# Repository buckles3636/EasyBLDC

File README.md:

# Easy BLDC

## Overview
Easy BLDC is an open source sensorless FOC brushless dc motor driver designed for propeller thrust applications such as drones or underwater AUVS.

## Features
* 30V Maximum Input Voltage
* 20A Maximum Continues Current (Untested)
* High current Amphenol power blade connector for board-board mounting
* High efficency FOC algorithm
* Modifiable parameters via Ti MotorWare® GUI

## Why FOC?
FOC is the most advanced of the three common algorithms. Unlike trapezoidal or sinusoidal control, which energize the motor’s phases based on predefined waveforms, FOC actively keeps tracks the stator position. This allows for precise control of both torque and speed by decoupling the motor’s magnetic field into two components: one that controls the motor's flux and the other that controls the torque. FOC is extremely efficient, especially at higher speeds, and results in smooth operation at lower speeds. 

## Key Components
* Texas Instruments DRV8305 gate driver
* Texas Instruments InstaSpin® TMS320F28027F MCU

## Ordering Guide
TODO:

## Getting Started Guide
TODO:

## Motor Tuning Guide
TODO:

## Contribution Guidelines
We welcome contributions from the broader community. To contribute:

1. **Fork the Repository**: Create your own fork of the project.
2. **Create a Feature Branch**: Make your changes in a new branch.
3. **Commit Your Changes**: Commit your changes with clear and detailed commit messages.
4. **Submit a Pull Request**: Create a pull request for your changes to be reviewed.

Please ensure your designs meet common standards and include necessary documentation and comments.

## Project Status
- Version 1: Released
- Version 2: In  Progress

## License
This project is licensed under the [MIT License](LICENSE) - see the LICENSE file for details.

## Contact
- Designer: Peter Buckley
- Email: peterbuckley3636@gmail.com

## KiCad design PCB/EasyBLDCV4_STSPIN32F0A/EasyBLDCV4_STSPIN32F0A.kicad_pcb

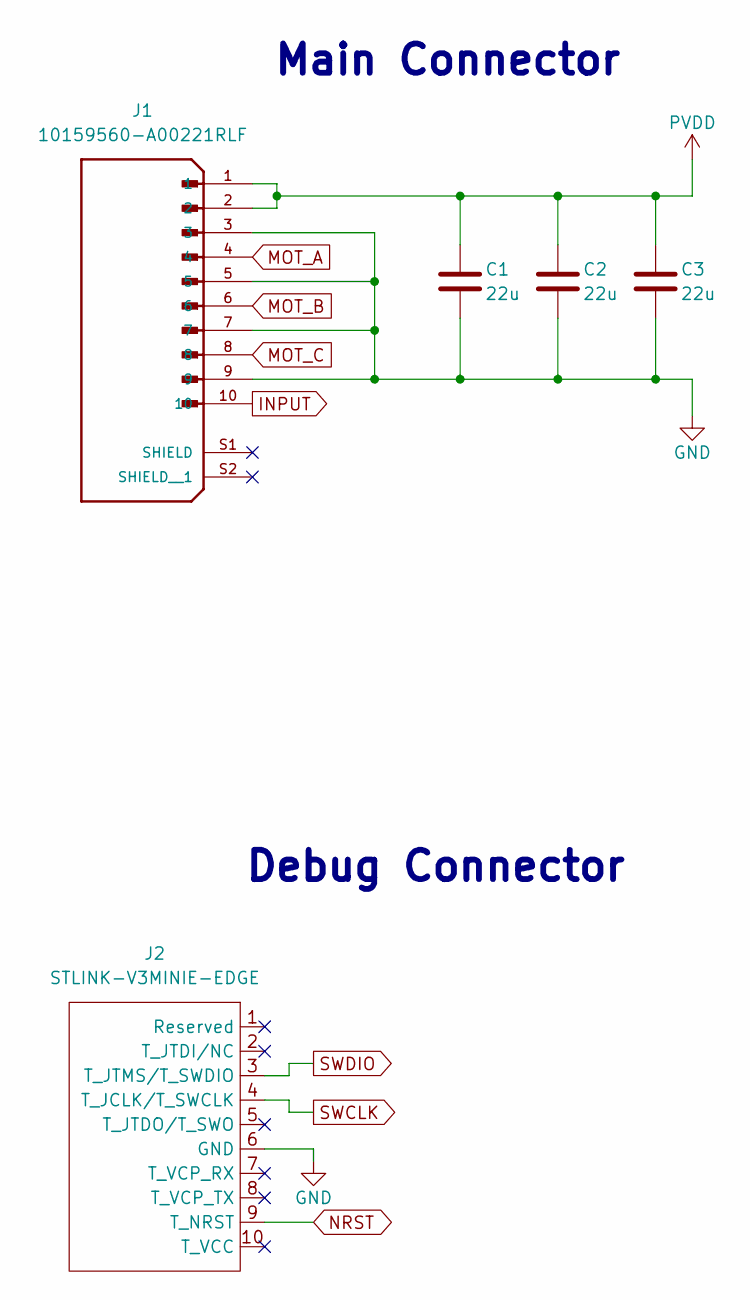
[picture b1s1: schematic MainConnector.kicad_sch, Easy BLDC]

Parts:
C1, C2, C3: 22u; C_1206_3216Metric
J1: 10159560-A00221RLF; AMPHENOL_10159560-A00221RLF; PARTREV C
J2: STLINK-V3MINIE-EDGE

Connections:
GND: C1.2, C2.2, C3.2, J1.3, J1.5, J1.7, J1.9, J2.6 (GND); also elsewhere on the board
INPUT: J1.10
MOT_A: J1.4; also elsewhere on the board
MOT_B: J1.6; also elsewhere on the board
MOT_C: J1.8; also elsewhere on the board
NRST: J2.9 (T_NRST); also elsewhere on the board
PVDD: C1.1, C2.1, C3.1, J1.1, J1.2; also elsewhere on the board
SWCLK: J2.4 (T_JCLK/T_SWCLK); also elsewhere on the board
SWDIO: J2.3 (T_JTMS/T_SWDIO); also elsewhere on the board

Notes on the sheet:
Main Connector
Debug Connector

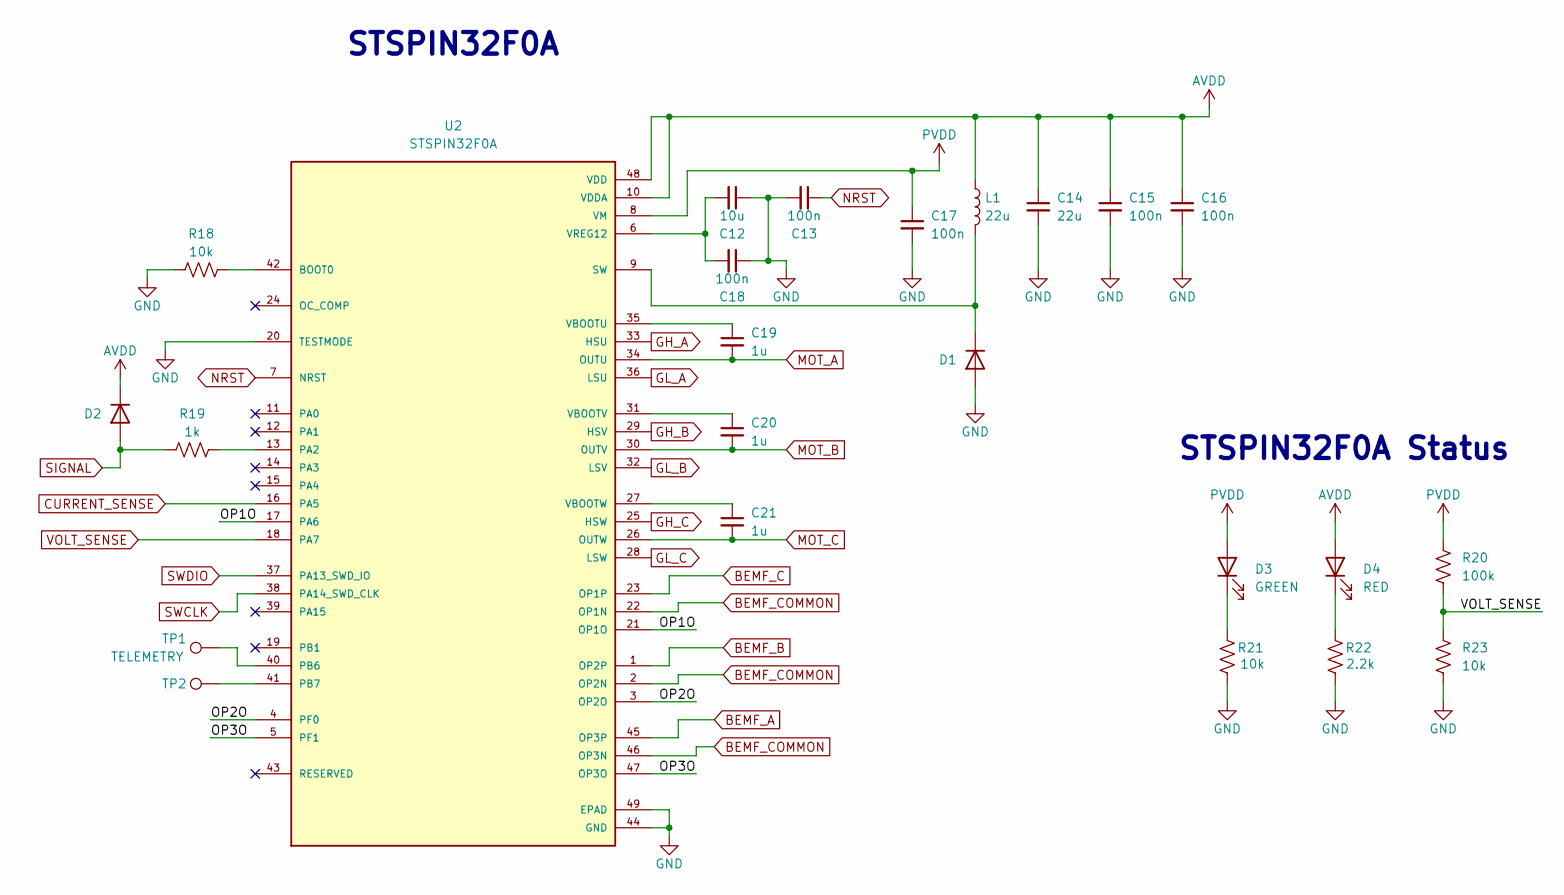
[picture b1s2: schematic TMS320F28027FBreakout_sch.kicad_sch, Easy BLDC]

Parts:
C12: 10u; C_0805_2012Metric
C13, C15, C16, C17, C18: 100n; C_0402_1005Metric
C14: 22u; C_0805_2012Metric
C19, C20, C21: 1u; C_0402_1005Metric
D1, D2: D; D_0402_1005Metric
D3: GREEN; LED_0603_1608Metric
D4: RED; LED_0603_1608Metric
L1: 22u; L_0805_2012Metric
R18, R21, R23: 10k; R_0402_1005Metric
R19: 1k; R_0402_1005Metric
R20: 100k; R_0402_1005Metric
R22: 2.2k; R_0402_1005Metric
TP1: TELEMETRY; TestPoint_Pad_D1.5mm
TP2: TestPoint; TestPoint_Pad_D1.5mm
U2: STSPIN32F0A; IC_STSPIN32F0A; PARTREV 2

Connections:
/MCU/OP1O: U2.17 (PA6), U2.21 (OP1O)
/MCU/OP2O: U2.3 (OP2O), U2.4 (PF0)
/MCU/OP3O: U2.5 (PF1), U2.47 (OP3O)
AVDD: C14.1, C15.1, C16.1, D2.1 (K), D4.2 (A), L1.1, U2.10 (VDDA), U2.48 (VDD); also elsewhere on the board
BEMF_A: U2.45 (OP3P); also elsewhere on the board
BEMF_B: U2.1 (OP2P); also elsewhere on the board
BEMF_C: U2.23 (OP1P); also elsewhere on the board
BEMF_COMMON: U2.2 (OP2N), U2.22 (OP1N), U2.46 (OP3N); also elsewhere on the board
CURRENT_SENSE: U2.16 (PA5); also elsewhere on the board
GH_A: U2.33 (HSU); also elsewhere on the board
GH_B: U2.29 (HSV); also elsewhere on the board
GH_C: U2.25 (HSW); also elsewhere on the board
GL_A: U2.36 (LSU); also elsewhere on the board
GL_B: U2.32 (LSV); also elsewhere on the board
GL_C: U2.28 (LSW); also elsewhere on the board
GND: C12.1, C13.2, C14.2, C15.2, C16.2, C17.2, C18.1, D1.2 (A), R18.1, R21.1, R22.1, R23.2, U2.20 (TESTMODE), U2.44 (GND), U2.49 (EPAD); also elsewhere on the board
MOT_A: C19.2, U2.34 (OUTU); also elsewhere on the board
MOT_B: C20.2, U2.30 (OUTV); also elsewhere on the board
MOT_C: C21.2, U2.26 (OUTW); also elsewhere on the board
NRST: C13.1, U2.7 (NRST); also elsewhere on the board
unnamed: D1.1 (K), L1.2, U2.9 (SW)
unnamed: D3.1 (K), R21.2
unnamed: D4.1 (K), R22.2
unnamed: R18.2, U2.42 (BOOT0)
unnamed: R19.2, U2.13 (PA2)
unnamed: TP1.1, U2.40 (PB6)
unnamed: TP2.1, U2.41 (PB7)
unnamed: C19.1, U2.35 (VBOOTU)
unnamed: C20.1, U2.31 (VBOOTV)
unnamed: C21.1, U2.27 (VBOOTW)
unnamed: C12.2, C18.2, U2.6 (VREG12)
PVDD: C17.1, D3.2 (A), R20.1, U2.8 (VM); also elsewhere on the board
SIGNAL: D2.2 (A), R19.1
SWCLK: U2.38 (PA14_SWD_CLK); also elsewhere on the board
SWDIO: U2.37 (PA13_SWD_IO); also elsewhere on the board
VOLT_SENSE: R20.2, R23.1, U2.18 (PA7)

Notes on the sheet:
STSPIN32F0A Status
STSPIN32F0A

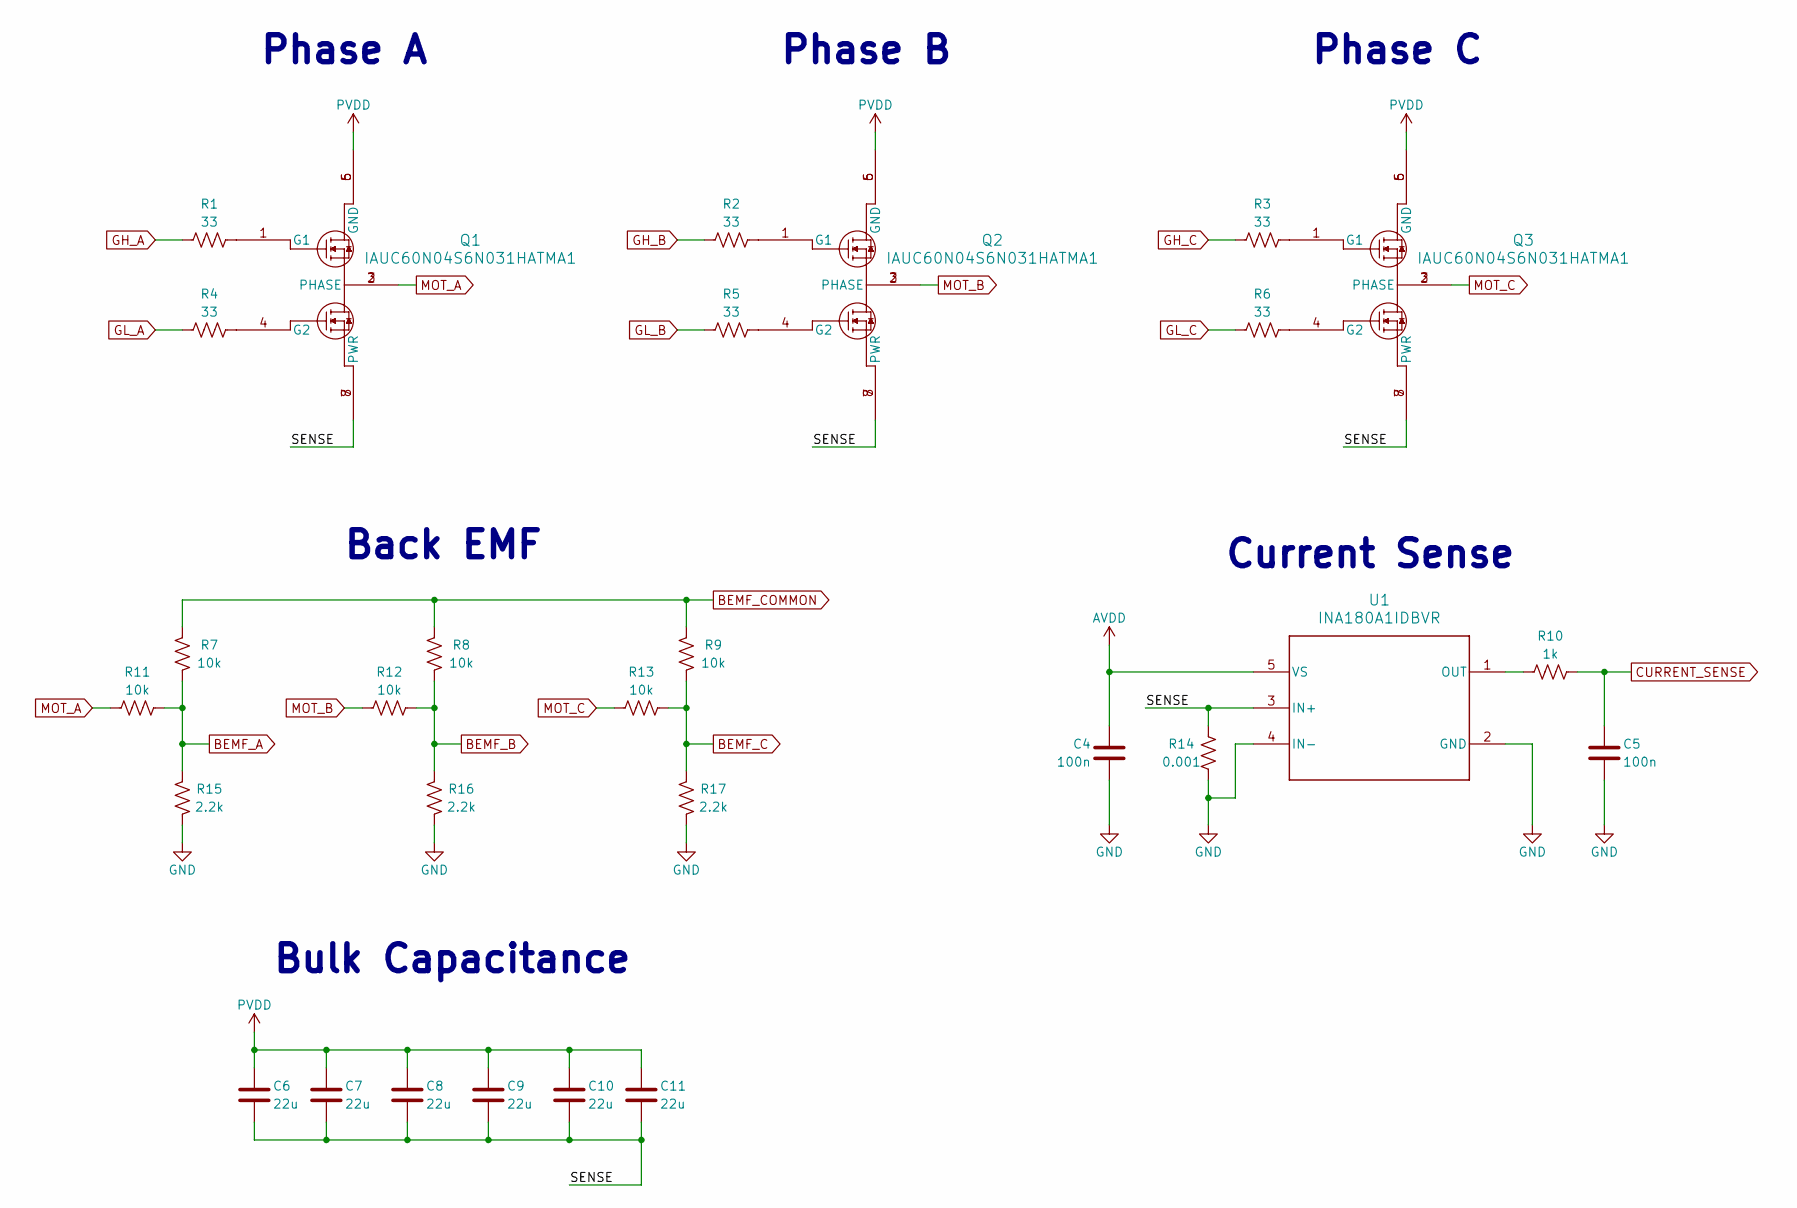
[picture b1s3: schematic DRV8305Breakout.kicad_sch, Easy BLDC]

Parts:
C4, C5: 100n; C_0402_1005Metric
C6, C7, C8, C9, C10, C11: 22u; C_1206_3216Metric
Q1, Q2, Q3: IAUC60N04S6N031HATMA1; PG-TDSON-8-56-2
R1, R2, R3, R4, R5, R6: 33; R_0402_1005Metric
R7, R8, R9, R11, R12, R13: 10k; R_0402_1005Metric
R10: 1k; R_0402_1005Metric
R14: 0.001; R_2512_6332Metric
R15, R16, R17: 2.2k; R_0402_1005Metric
U1: INA180A1IDBVR; DBV0005A_N

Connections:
/Power Stage/SENSE: C6.2, C7.2, C8.2, C9.2, C10.2, C11.2, Q1.7 (PWR), Q1.8 (PWR), Q2.7 (PWR), Q2.8 (PWR), Q3.7 (PWR), Q3.8 (PWR), R14.2, U1.3 (IN+)
AVDD: C4.1, U1.5 (VS); also elsewhere on the board
BEMF_A: R7.1, R11.2, R15.2; also elsewhere on the board
BEMF_B: R8.1, R12.2, R16.2; also elsewhere on the board
BEMF_C: R9.1, R13.2, R17.2; also elsewhere on the board
BEMF_COMMON: R7.2, R8.2, R9.2; also elsewhere on the board
CURRENT_SENSE: C5.1, R10.2; also elsewhere on the board
GH_A: R1.1; also elsewhere on the board
GH_B: R2.1; also elsewhere on the board
GH_C: R3.1; also elsewhere on the board
GL_A: R4.1; also elsewhere on the board
GL_B: R5.1; also elsewhere on the board
GL_C: R6.1; also elsewhere on the board
GND: C4.2, C5.2, R14.1, R15.1, R16.1, R17.1, U1.2 (GND), U1.4 (IN-); also elsewhere on the board
MOT_A: Q1.2 (PHASE), Q1.3 (PHASE), R11.1; also elsewhere on the board
MOT_B: Q2.2 (PHASE), Q2.3 (PHASE), R12.1; also elsewhere on the board
MOT_C: Q3.2 (PHASE), Q3.3 (PHASE), R13.1; also elsewhere on the board
unnamed: Q1.1 (G1), R1.2
unnamed: Q1.4 (G2), R4.2
unnamed: Q2.1 (G1), R2.2
unnamed: Q2.4 (G2), R5.2
unnamed: Q3.1 (G1), R3.2
unnamed: Q3.4 (G2), R6.2
unnamed: R10.1, U1.1 (OUT)
PVDD: C6.1, C7.1, C8.1, C9.1, C10.1, C11.1, Q1.5 (GND), Q1.6 (GND), Q2.5 (GND), Q2.6 (GND), Q3.5 (GND), Q3.6 (GND); also elsewhere on the board

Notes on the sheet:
Current Sense
Phase C
Bulk Capacitance
Phase B
Back EMF
Phase A

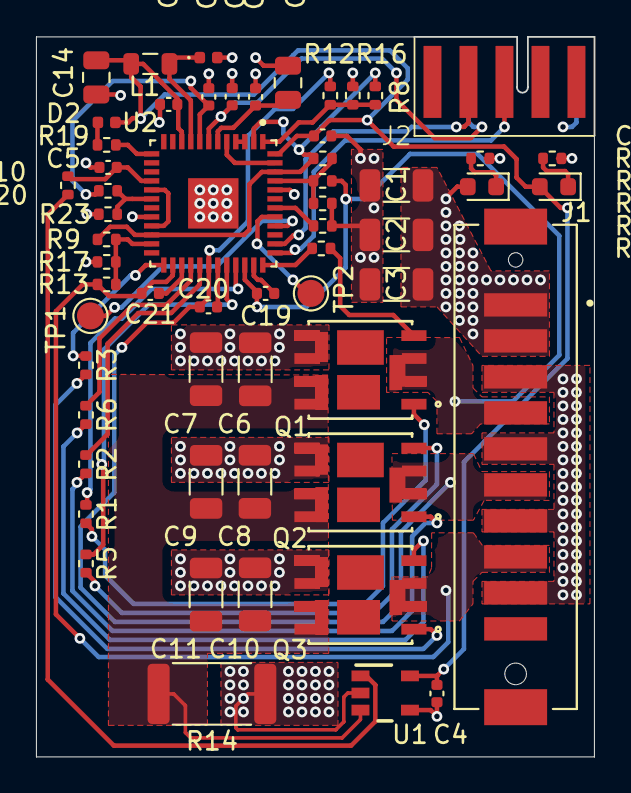
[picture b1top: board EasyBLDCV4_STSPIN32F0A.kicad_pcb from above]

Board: 4 copper layers, 31.0 x 40.0 mm, 58 parts (0 on the bottom side), 44 nets.

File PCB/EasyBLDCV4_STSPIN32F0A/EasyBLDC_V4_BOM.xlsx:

Designator | Footprint | Quantity | Value | Part #
C1, C10, C11, C2, C3, C6, C7, C8, C9 | 1206 | 9 | 22u 25V | CL31A226KAHNNNE
C12 | 805 | 1 | 10u 6.3V | CL21B106KQQNNNE
C13, C15, C16, C18, C4, C5 | 402 | 6 | 100n 6.3V | GRM155R60J104KA01D
C14 | 805 | 1 | 22u 6.3V | CL21A226MQQNNNE
C17 | 402 | 1 | 100n 25V | CL05B104KA5NNNC
C19, C20, C21 | 402 | 3 | 1u 25V | GRM155R61E105MA12D
D1, D2 | 402 | 2 | D | BAT54LP-7
D3 | 603 | 1 | GREEN | 150060GS75000
D4 | 603 | 1 | RED | 150060RS75000
J1 | AMPHENOL_10159560-A00221RLF | 1 |  | 10159560-A00221RLF
J2 | STLINK-V3MINIE-EDGE | 1 | STLINK-V3MINIE-EDGE
L1 |  | 1 | 22uF | MLZ2012P220WT000
Q1, Q2, Q3 | PG-TDSON-8-56-2 | 3 |  | IAUC60N04S6N031HATMA1
R1, R2, R3, R4, R5, R6 | 402 | 6 | 33 | RC0402FR-0733RL
R10, R19 | 402 | 2 | 1k | RC0402JR-071KL
R11, R12, R13, R18, R23, R7, R8, R9, R21 | 402 | 9 | 10k | RC0402JR-0710KL
R14 | 2512 | 1 | 1E-3 | CRE2512-FZ-R001E-2
R15, R16, R17, R22 | 402 | 4 | 2.2k | RC0402FR-132K2L
R20 | 402 | 1 | 100k | RC0402JR-07100KL
TP1 | TestPoint_Pad_D1.5mm | 1 | TELEMETRY
TP2 | TestPoint_Pad_D1.5mm | 1 | TestPoint
U1 | DBV0005A_N | 1 |  | INA180A1IDBVR
U2 | IC_STSPIN32F0A | 1 |  | STSPIN32F0ATR

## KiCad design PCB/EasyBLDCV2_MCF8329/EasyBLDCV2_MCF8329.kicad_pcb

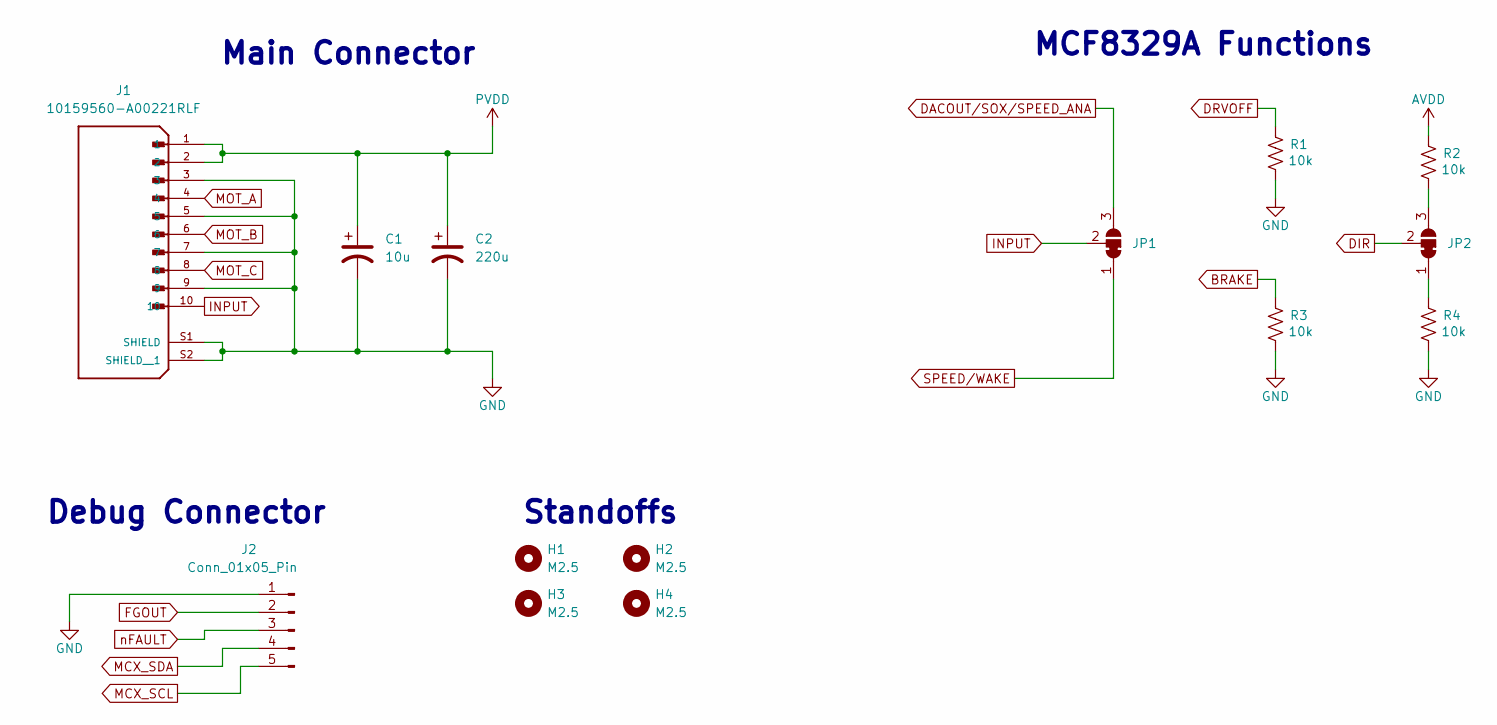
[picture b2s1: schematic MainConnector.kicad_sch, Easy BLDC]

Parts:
C1: 10u; CP_Elec_5x5.3
C2: 220u; CP_Elec_10x10.5
H1, H2, H3, H4: M2.5; MountingHole_2.7mm_M2.5_ISO7380
J1: 10159560-A00221RLF; AMPHENOL_10159560-A00221RLF; PARTREV C
J2: Conn_01x05_Pin; PinSocket_1x05_P2.54mm_Vertical
JP1, JP2: SolderJumper_3_Bridged12; SolderJumper-3_P1.3mm_Bridged12_RoundedPad1.0x1.5mm_NumberL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
R1, R2, R3, R4: 10k; R_0603_1608Metric

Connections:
AVDD: R2.2; also elsewhere on the board
BRAKE: R3.2; also elsewhere on the board
DACOUT/SOX/SPEED_ANA: JP1.3 (B); also elsewhere on the board
DIR: JP2.2 (C); also elsewhere on the board
DRVOFF: R1.2; also elsewhere on the board
FGOUT: J2.2; also elsewhere on the board
GND: C1.2, C2.2, J1.3, J1.5, J1.7, J1.9, J1.S1 (SHIELD), J1.S2 (SHIELD__1), J2.1, R1.1, R3.1, R4.1; also elsewhere on the board
INPUT: J1.10, JP1.2 (C)
MCX_SCL: J2.5; also elsewhere on the board
MCX_SDA: J2.4; also elsewhere on the board
MOT_A: J1.4; also elsewhere on the board
MOT_B: J1.6; also elsewhere on the board
MOT_C: J1.8; also elsewhere on the board
unnamed: JP2.1 (A), R4.2
unnamed: JP2.3 (B), R2.1
PVDD: C1.1, C2.1, J1.1, J1.2; also elsewhere on the board
SPEED/WAKE: JP1.1 (A); also elsewhere on the board
nFAULT: J2.3; also elsewhere on the board

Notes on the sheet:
MCF8329A Functions
Main Connector
Debug Connector
Standoffs

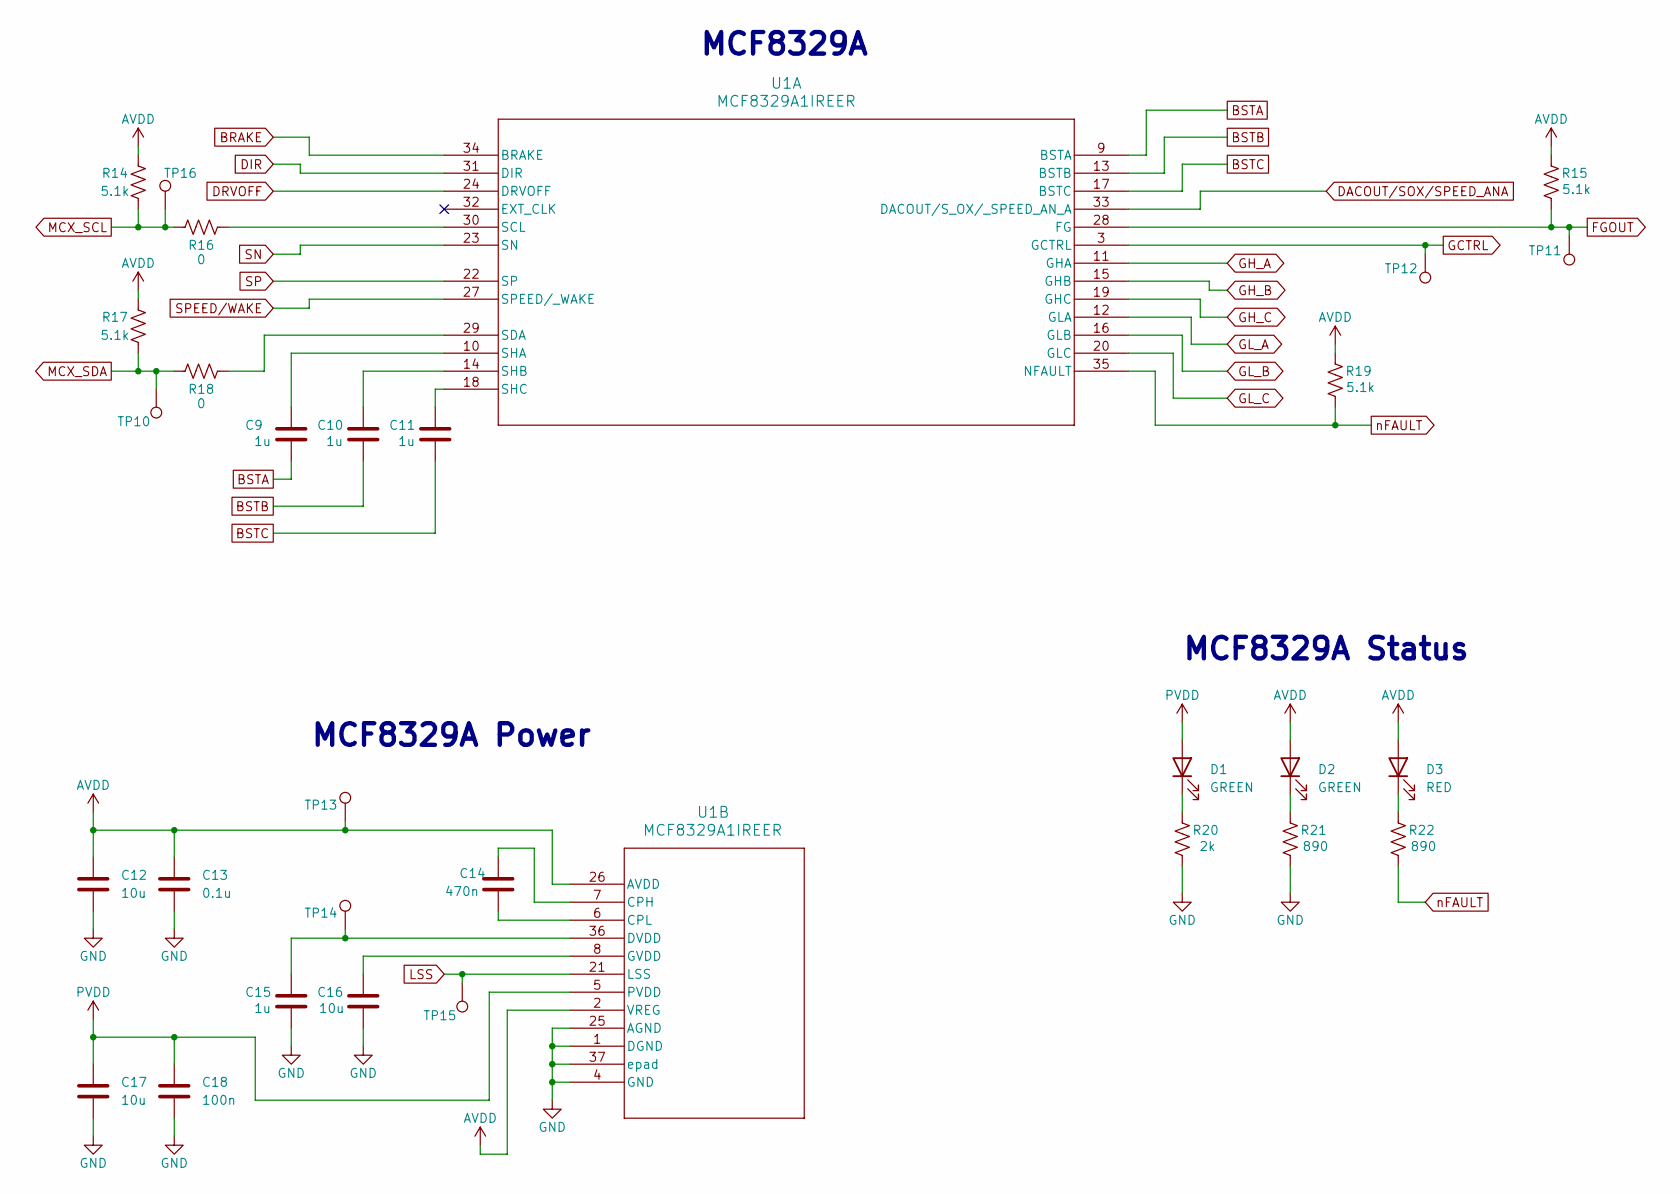
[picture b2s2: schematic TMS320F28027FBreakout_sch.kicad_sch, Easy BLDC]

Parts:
C9, C10, C11, C15: 1u; C_0603_1608Metric
C12, C16: 10u; C_0603_1608Metric
C13: 0.1u; C_0603_1608Metric
C14: 470n; C_0805_2012Metric
C17: 10u; C_2220_5750Metric
C18: 100n; C_0603_1608Metric
D1, D2: GREEN; LED_0805_2012Metric
D3: RED; LED_0805_2012Metric
R14, R15, R17, R19: 5.1k; R_0603_1608Metric
R16, R18: 0; R_0603_1608Metric
R20: 2k; R_0603_1608Metric
R21, R22: 890; R_0603_1608Metric
TP10, TP11, TP12, TP13, TP14, TP15, TP16: TestPoint; TestPoint_Pad_D1.5mm
U1: MCF8329A1IREER; WQFN36_REE_TEX

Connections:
AVDD: C12.1, C13.1, D2.2 (A), D3.2 (A), R14.2, R15.2, R17.2, R19.2, TP13.1, U1.2 (VREG), U1.26 (AVDD); also elsewhere on the board
BRAKE: U1.34 (BRAKE); also elsewhere on the board
BSTA: C9.2, U1.9 (BSTA)
BSTB: C10.2, U1.13 (BSTB)
BSTC: C11.2, U1.17 (BSTC)
DACOUT/SOX/SPEED_ANA: U1.33 (DACOUT/S_OX/_SPEED_AN_A); also elsewhere on the board
DIR: U1.31 (DIR); also elsewhere on the board
DRVOFF: U1.24 (DRVOFF); also elsewhere on the board
FGOUT: R15.1, TP11.1, U1.28 (FG); also elsewhere on the board
GCTRL: TP12.1, U1.3 (GCTRL)
GH_A: U1.11 (GHA); also elsewhere on the board
GH_B: U1.15 (GHB); also elsewhere on the board
GH_C: U1.19 (GHC); also elsewhere on the board
GL_A: U1.12 (GLA); also elsewhere on the board
GL_B: U1.16 (GLB); also elsewhere on the board
GL_C: U1.20 (GLC); also elsewhere on the board
GND: C12.2, C13.2, C15.2, C16.2, C17.2, C18.2, R20.1, R21.1, U1.1 (DGND), U1.4 (GND), U1.25 (AGND), U1.37 (epad); also elsewhere on the board
LSS: TP15.1, U1.21 (LSS); also elsewhere on the board
MCX_SCL: R14.1, R16.1, TP16.1; also elsewhere on the board
MCX_SDA: R17.1, R18.1, TP10.1; also elsewhere on the board
unnamed: D1.1 (K), R20.2
unnamed: D2.1 (K), R21.2
unnamed: D3.1 (K), R22.2
unnamed: R16.2, U1.30 (SCL)
unnamed: R18.2, U1.29 (SDA)
unnamed: C9.1, U1.10 (SHA)
unnamed: C10.1, U1.14 (SHB)
unnamed: C11.1, U1.18 (SHC)
unnamed: C14.1, U1.7 (CPH)
unnamed: C14.2, U1.6 (CPL)
unnamed: C15.1, TP14.1, U1.36 (DVDD)
unnamed: C16.1, U1.8 (GVDD)
PVDD: C17.1, C18.1, D1.2 (A), U1.5 (PVDD); also elsewhere on the board
SN: U1.23 (SN); also elsewhere on the board
SP: U1.22 (SP); also elsewhere on the board
SPEED/WAKE: U1.27 (SPEED/_WAKE); also elsewhere on the board
nFAULT: R19.1, R22.1, U1.35 (NFAULT); also elsewhere on the board

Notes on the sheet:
MCF8329A Status
MCF8329A
MCF8329A Power

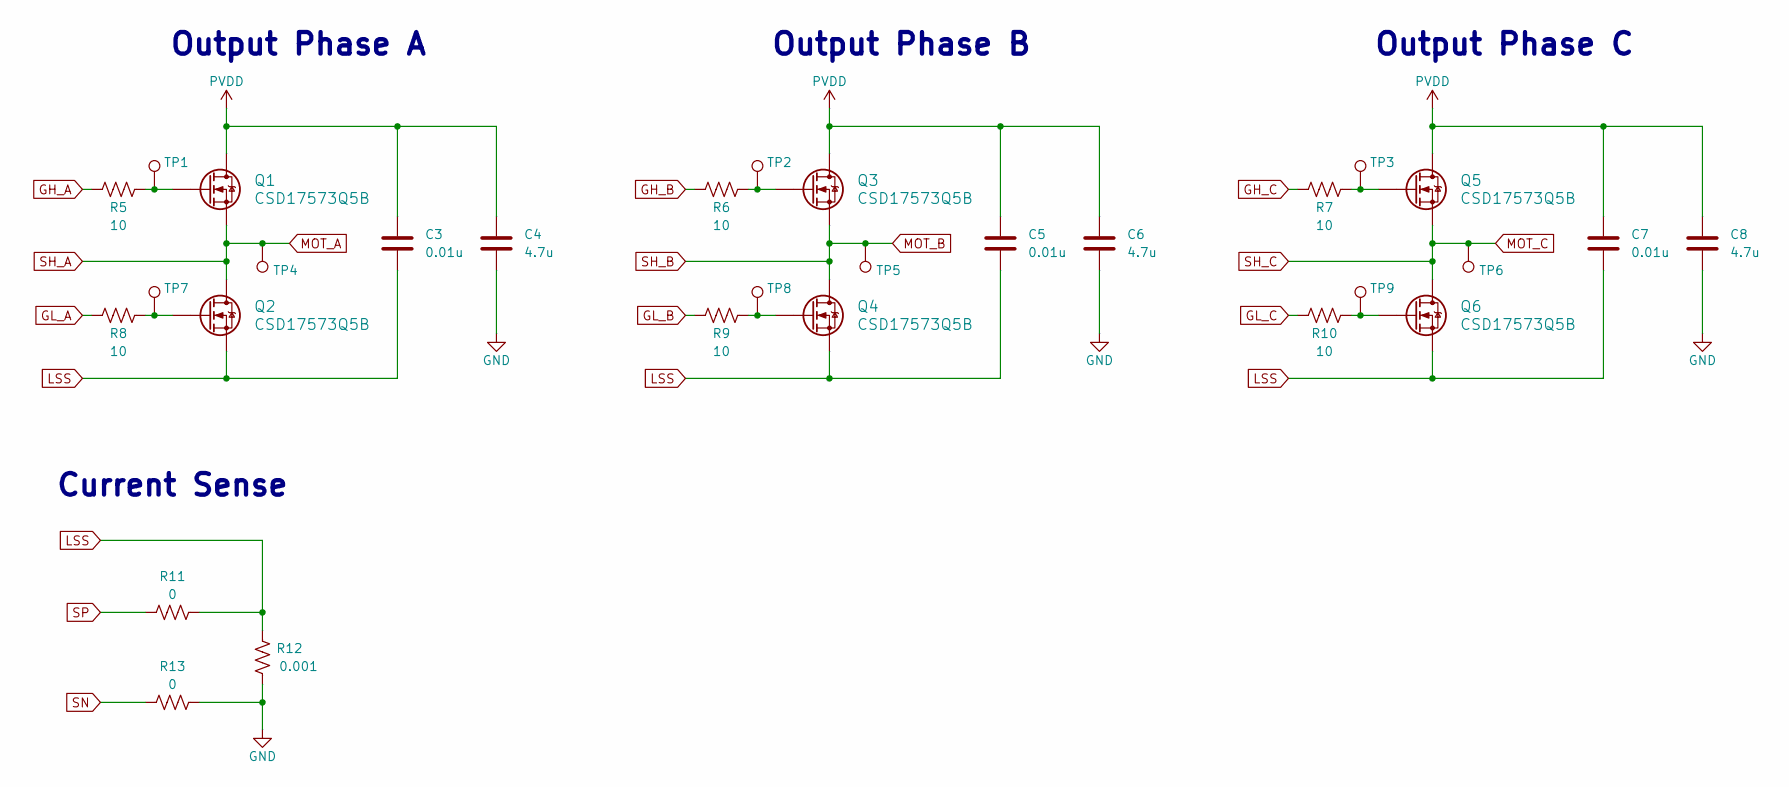
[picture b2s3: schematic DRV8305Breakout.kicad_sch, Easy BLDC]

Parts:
C3, C5, C7: 0.01u; C_0805_2012Metric
C4, C6, C8: 4.7u; C_1210_3225Metric
Q1, Q2, Q3, Q4, Q5, Q6: CSD17573Q5B; DNK0008A
R5, R6, R7, R8, R9, R10: 10; R_0603_1608Metric
R11, R13: 0; R_0603_1608Metric
R12: 0.001; R_0603_1608Metric
TP1, TP2, TP3, TP4, TP5, TP6, TP7, TP8, TP9: TestPoint; TestPoint_Pad_D1.5mm

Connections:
GH_A: R5.1; also elsewhere on the board
GH_B: R6.1; also elsewhere on the board
GH_C: R7.1; also elsewhere on the board
GL_A: R8.1; also elsewhere on the board
GL_B: R9.1; also elsewhere on the board
GL_C: R10.1; also elsewhere on the board
GND: C4.2, C6.2, C8.2, R12.1, R13.1; also elsewhere on the board
LSS: C3.2, C5.2, C7.2, Q2.1 (S), Q2.2 (S), Q2.3 (S), Q4.1 (S), Q4.2 (S), Q4.3 (S), Q6.1 (S), Q6.2 (S), Q6.3 (S), R11.1, R12.2; also elsewhere on the board
MOT_A: Q1.1 (S), Q1.2 (S), Q1.3 (S), Q2.5 (D), Q2.6 (D), Q2.7 (D), Q2.8 (D), TP4.1; also elsewhere on the board
MOT_B: Q3.1 (S), Q3.2 (S), Q3.3 (S), Q4.5 (D), Q4.6 (D), Q4.7 (D), Q4.8 (D), TP5.1; also elsewhere on the board
MOT_C: Q5.1 (S), Q5.2 (S), Q5.3 (S), Q6.5 (D), Q6.6 (D), Q6.7 (D), Q6.8 (D), TP6.1; also elsewhere on the board
unnamed: Q1.4 (G), R5.2, TP1.1
unnamed: Q2.4 (G), R8.2, TP7.1
unnamed: Q3.4 (G), R6.2, TP2.1
unnamed: Q4.4 (G), R9.2, TP8.1
unnamed: Q5.4 (G), R7.2, TP3.1
unnamed: Q6.4 (G), R10.2, TP9.1
PVDD: C3.1, C4.1, C5.1, C6.1, C7.1, C8.1, Q1.5 (D), Q1.6 (D), Q1.7 (D), Q1.8 (D), Q3.5 (D), Q3.6 (D), Q3.7 (D), Q3.8 (D), Q5.5 (D), Q5.6 (D), Q5.7 (D), Q5.8 (D); also elsewhere on the board
SN: R13.2; also elsewhere on the board
SP: R11.2; also elsewhere on the board

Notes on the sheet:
Output Phase C
Current Sense
Output Phase A
Output Phase B

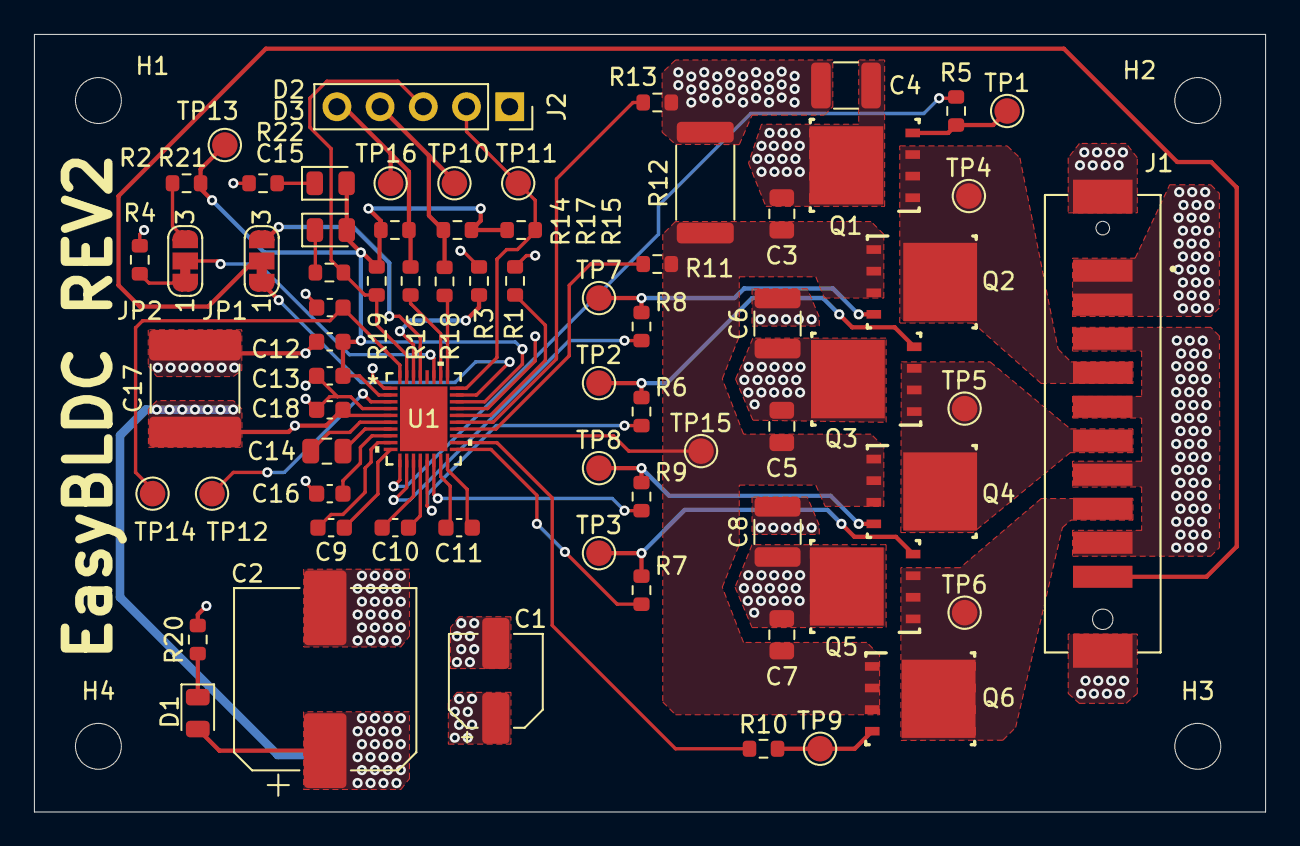
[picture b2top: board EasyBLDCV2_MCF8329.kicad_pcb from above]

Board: 4 copper layers, 72.4 x 45.7 mm, 74 parts (0 on the bottom side), 49 nets.

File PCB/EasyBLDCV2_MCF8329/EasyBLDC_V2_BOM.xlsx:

Designator | Quantity | Value | Description | Package Reference | Part Number | Manufacturer
C1 | 1 | 10uF | CAP, AL, 10uF, 50V, +/-20% | 0.209" L x 0.209" W | 865080642006
C2 | 1 | 220uF | CAP, AL, 220uF, 50V, +/-20% | 0.406" L x 0.406" W | UCW1H221MNL1GS
C3, C5, C7 | 3 | 0.01uF | CAP, CERM, 0.01 uF, 50 V, +/- 5%, X7R, 0805 | 805
C4, C6, C8 | 3 | 4.7uF | CAP, CERM, 4.7 uF, 50 V, +/- 10%, X7S, 1210 | 1210
C9, C10, C11, C15 | 4 | 1uF | CAP, CERM, 1 uF, 25 V, +/- 10%, X5R, 0603 | 603 | C1608X5R1E105K080AC
C12 | 1 | 10uF | CAP, CERM, 10 uF, 6.3 V, +/- 20%, X5R, 0603 | 603 | C0603C106M9PACTU
C13 | 1 | 0.1uF | CAP, CERM, 0.1 µF, 6.3 V,+/- 10%, X5R, 0603 | 603 | C0603C104K9PAC7867
C14 | 1 | 470nF | CAP, CERM, 0.47 uF, 50 V, +/- 10%, X7R, 0805 | 805
C16 | 1 | 10uF | CAP, CERM, 10 uF, 25 V, +/- 20%, X5R, 0603 | 605 | C1608X5R1E106M080AC
C17 | 1 | 10uF | CAP, CERM, 10 uF, 50 V, +/- 20%, X7R, 2220 | 2220
C18 | 1 | 0.1uF | CAP, CERM, 0.1 uF, 50 V, +/- 10%, X7R, 0603 | 603
D1, D2 | 2 | Green | LED, Green, SMD | LED_0805 | LTST-C170KGKT
D3 | 1 | Red | LED, Red, SMD | LED_0805
J1 | 1 |  | POWERSTAK VERTICAL HEADER 10POS | Custom | 10159560-A00221RLF
J2 | 1 |  | CONN HEADER SMD R/A 5POS 2.54MM | Custom | TSM-105-01-T-SH
U1 | 1 |  | IC GATE DRVR HALF-BRIDGE 36WQFN | Custom | MCF8329A1IREER
Q1, Q2, Q3, Q4, Q5, Q6 | 6 |  | N-Channel 30 V 100A (Ta) 3.2W (Ta), 195W (Tc) Surface Mount 8-VSON-CLIP (5x6) | 8VSON | CSD17573Q5B
R12 | 1 | 1E-3 | RES, 0.001, 1%, 4 W, RES_2725 | RES_2725 | CSS2725FT1L00

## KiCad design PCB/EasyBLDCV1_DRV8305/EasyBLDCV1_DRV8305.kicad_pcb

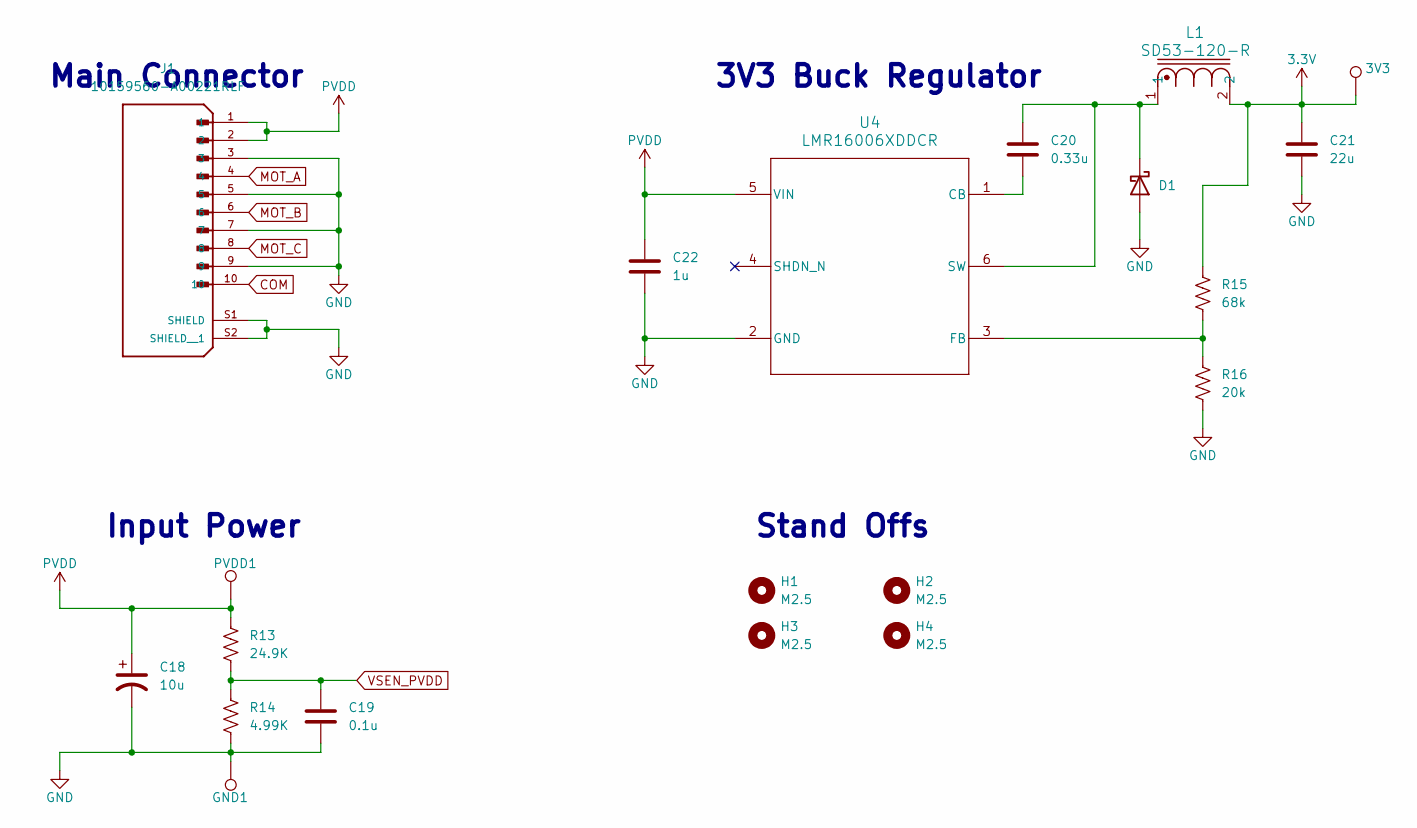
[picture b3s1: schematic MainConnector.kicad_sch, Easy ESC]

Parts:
3V3: TestPoint; TestPoint_Pad_D2.0mm
C18: 10u; C_1210_3225Metric
C19: 0.1u; C_0402_1005Metric
C20: 0.33u; C_0603_1608Metric
C21: 22u; C_0603_1608Metric
C22: 1u; C_0603_1608Metric
D1: D_Schottky; D_SOD-123
GND1: TestPoint; TestPoint_Pad_D2.0mm
H1, H2, H3, H4: M2.5; MountingHole_2.7mm_M2.5_ISO7380
J1: 10159560-A00221RLF; AMPHENOL_10159560-A00221RLF; PARTREV C
L1: SD53-120-R; L_Changjiang_FNR4020S
PVDD1: TestPoint; TestPoint_Pad_D2.0mm
R13: 24.9K; R_0603_1608Metric
R14: 4.99K; R_0402_1005Metric
R15: 68k; R_0603_1608Metric
R16: 20k; R_0603_1608Metric
U4: LMR16006XDDCR; DDC0006A

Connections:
3.3V: 3V3.1, C21.1, L1.2, R15.1; also elsewhere on the board
COM: J1.10; also elsewhere on the board
GND: C18.2, C19.2, C21.2, C22.2, D1.2 (A), GND1.1, J1.3, J1.5, J1.7, J1.9, J1.S1 (SHIELD), J1.S2 (SHIELD__1), R14.2, R16.2, U4.2 (GND); also elsewhere on the board
MOT_A: J1.4; also elsewhere on the board
MOT_B: J1.6; also elsewhere on the board
MOT_C: J1.8; also elsewhere on the board
unnamed: C20.1, D1.1 (K), L1.1, U4.6 (SW)
unnamed: C20.2, U4.1 (CB)
unnamed: R15.2, R16.1, U4.3 (FB)
PVDD: C18.1, C22.1, J1.1, J1.2, PVDD1.1, R13.1, U4.5 (VIN); also elsewhere on the board
VSEN_PVDD: C19.1, R13.2, R14.1; also elsewhere on the board

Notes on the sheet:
Stand Offs
Main Connector
Input Power
3V3 Buck Regulator
